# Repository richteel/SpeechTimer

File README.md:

# SpeechTimer
Clock/Timer for Speeches

# Folder Structure #

There are several folders in this project. Below is a brief description of each one.

- **CircuitPython:** An early prototype with a web interface. It works but is unstable due to memory fragmentation. It is no longer being developed. It is kept here if anyone using Python wants to use it or improve upon it.
- **Documentation:** Some documentation used during development along with user guide and other miscellaneous materials.
	- **Speech Timer - Developer Guide.docx:** Not much here at the moment. *(Just a placeholder)*
	- **Speech Timer - User Guide.docx:** Very basic user guide showing how to use the remote.
- **PCB:** Eagle project with schematic and PCB design. This is for the development version, which incorporates two Raspberry Pi Pico boards. A regular Raspberry Pi Pico as a Picoprobe and a Raspberry Pi Pico W as the micro-controller running the show.
- **SD Card:** Contents for the micro SD card.
- **SpeechTimer:** The Arduino Sketch C++ project written using the Arduino IDE. Currently everything seems to be working, but the Web Interface has not been created yet.

# Parts List #

- Raspberry Pi Pico
	- Quantity: 1
	- Note: Used as Picoprobe for programming and debugging
- Raspberry Pi Pico W
	- Quantity: 1
- 5mm Neopixels (Through hole)
	- Quantity: 58
	- Source(s): [Adafruit](https://www.adafruit.com/product/1938) / [AliExpress](https://www.aliexpress.us/item/3256804752897372.html?spm=a2g0o.order_list.order_list_main.18.3df818029J6f3W&gatewayAdapt=glo2usa)
- SD Card Breakout
	- Quantity: 1
	- Source(s): [Adafruit](https://www.adafruit.com/product/4682)
- Monochrome 0.96" 128x54 OLED Display
	- Quantity: 1
	- Source(s): [Adafruit](https://www.adafruit.com/product/326) / [Amazon](https://www.amazon.com/gp/product/B08VNRH5HR/ref=ppx_yo_dt_b_search_asin_image?ie=UTF8&th=1)
- Remote
	- Quantity: 1
	- Source(s): [Amazon](https://www.amazon.com/gp/product/B0C7BPJYH1/ref=ppx_yo_dt_b_search_asin_image?ie=UTF8&psc=1)
- 2.54mm (0.1") JST Connectors (3, 4, & 6 position)
	- Quantity: 1 each 3-position, 4-position, and 6-position
	- Source(s): [Amazon](https://www.amazon.com/gp/product/B015Y6JOUG/ref=ppx_yo_dt_b_search_asin_image?ie=UTF8&psc=1) / [AliExpress](https://www.aliexpress.us/item/2251832778234720.html?spm=a2g0o.order_detail.order_detail_item.2.2908f19cEtDDFD&gatewayAdapt=glo2usa)
- 2.54mm (0.1") Female Headers
	- Quantity: 5 (4 20-position, 1 9-position)
	- Source(s): [Adafruit](https://www.adafruit.com/product/598)
- 2.54mm (0.1") Male Headers
	- Quantity: 5 (4 20-position, 1 9-position)
	- Source(s): [Adafruit](https://www.adafruit.com/product/2671)
- Momentary Push Button Switch (N.O.) 6mm slim
	- Quantity: 2
	- Source(s): [Adafruit](https://www.adafruit.com/product/1489)
- IR Receiver TSOP38238
	- Quantity: 1
	- Source(s): [Adafruit](https://www.adafruit.com/product/157) / [AliExpress](https://www.aliexpress.us/item/2251832658861424.html?spm=a2g0o.order_list.order_list_main.12.3df818029J6f3W&gatewayAdapt=glo2usa)
- IR LED 5mm
	- Quantity: 1
	- Source(s): [Adafruit](https://www.adafruit.com/product/388)
- Red LED 3mm
	- Quantity: 1
	- Source(s): [Adafruit](https://www.adafruit.com/product/777)
- CdS Photoresistor
	- Quantity: 1
	- Source(s): [Adafruit](https://www.adafruit.com/product/161)

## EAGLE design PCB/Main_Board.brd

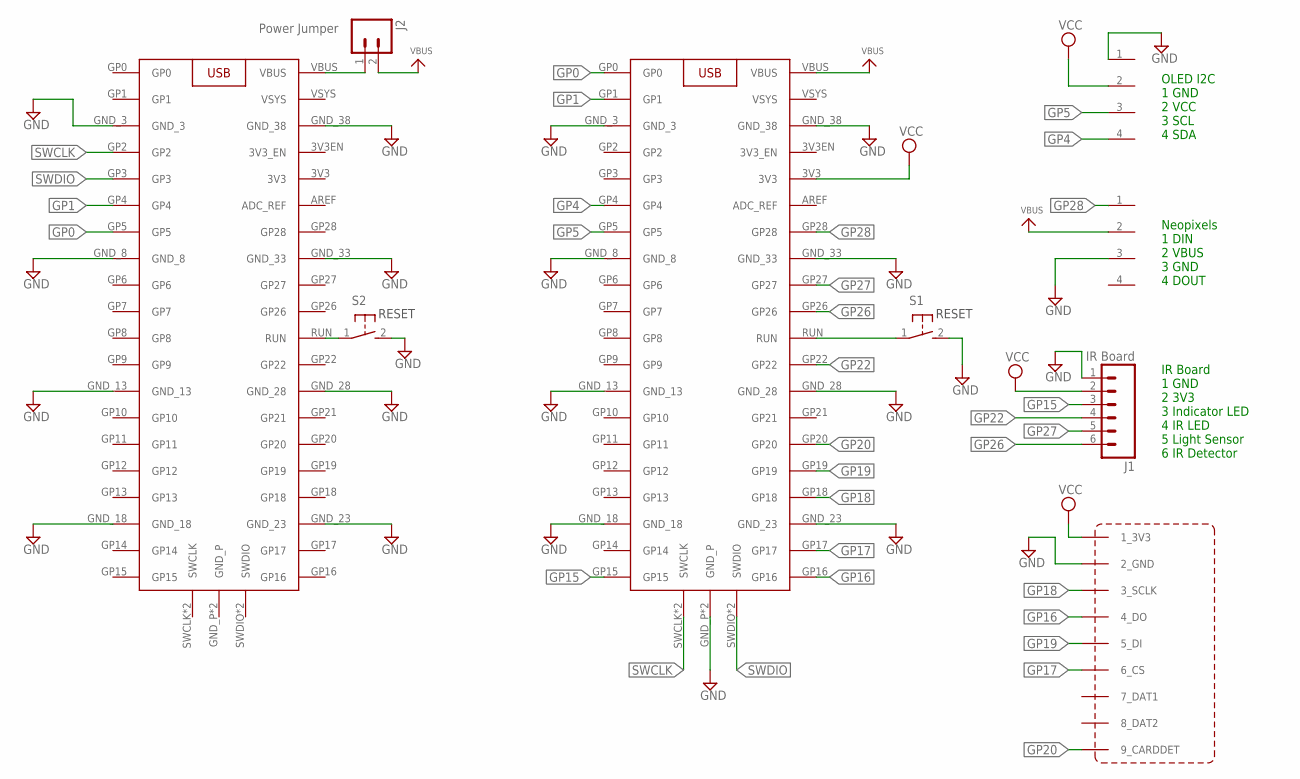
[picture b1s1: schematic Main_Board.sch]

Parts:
J1: IR Board; 1X06_LONGPADS
J2: Power Jumper; 1X02_LOCK_LONGPADS
S1, S2: RESET; ADAFRUIT_SW_1489
SDCARD2: ADAFRUIT_SDCARD3V3THROUGHHOLE; ADAFRUIT_SDCARD3V3
U$1, U$2: RASPBERRY_PI_PICORASPBERRY_PI_PICO_&_W; RASPBERRY_PI_PICO_N_W
U$3, U$4: HEADER-1X4

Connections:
GND: J1.1, S1.2 (S), S2.2 (S), SDCARD2.2_GND, U$1.GND_3, U$1.GND_8, U$1.GND_13, U$1.GND_18, U$1.GND_23, U$1.GND_28, U$1.GND_33, U$1.GND_38, U$1.GND_P, U$1.GND_P1 (GND_P), U$2.GND_3, U$2.GND_8, U$2.GND_13, U$2.GND_18, U$2.GND_23, U$2.GND_28, U$2.GND_33, U$2.GND_38, U$3.3, U$4.1
GP0: U$1.GP0, U$2.GP5
GP1: U$1.GP1, U$2.GP4
GP4: U$1.GP4, U$4.4
GP5: U$1.GP5, U$4.3
GP15: J1.3, U$1.GP15
GP16: SDCARD2.4_DO, U$1.GP16
GP17: SDCARD2.6_CS, U$1.GP17
GP18: SDCARD2.3_SCLK, U$1.GP18
GP19: SDCARD2.5_DI, U$1.GP19
GP20: SDCARD2.9_CARDDET, U$1.GP20
GP22: J1.4, U$1.GP22
GP26: J1.6, U$1.GP26
GP27: J1.5, U$1.GP27
GP28: U$1.GP28, U$3.1
unnamed: S2.1, U$2.RUN
unnamed: J2.1, U$2.VBUS
unnamed: S1.1, U$1.RUN
SWCLK: U$1.SWCLK, U$1.SWCLK1 (SWCLK), U$2.GP2
SWDIO: U$1.SWDIO, U$1.SWDIO1 (SWDIO), U$2.GP3
VBUS: J2.2, U$1.VBUS, U$3.2
VCC: J1.2, SDCARD2.1_3V3, U$1.3V3, U$4.2

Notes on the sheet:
Neopixels 1 DIN 2 VBUS 3 GND 4 DOUT
OLED I2C 1 GND 2 VCC 3 SCL 4 SDA
IR Board 1 GND 2 3V3 3 Indicator LED 4 IR LED 5 Light Sensor 6 IR Detector

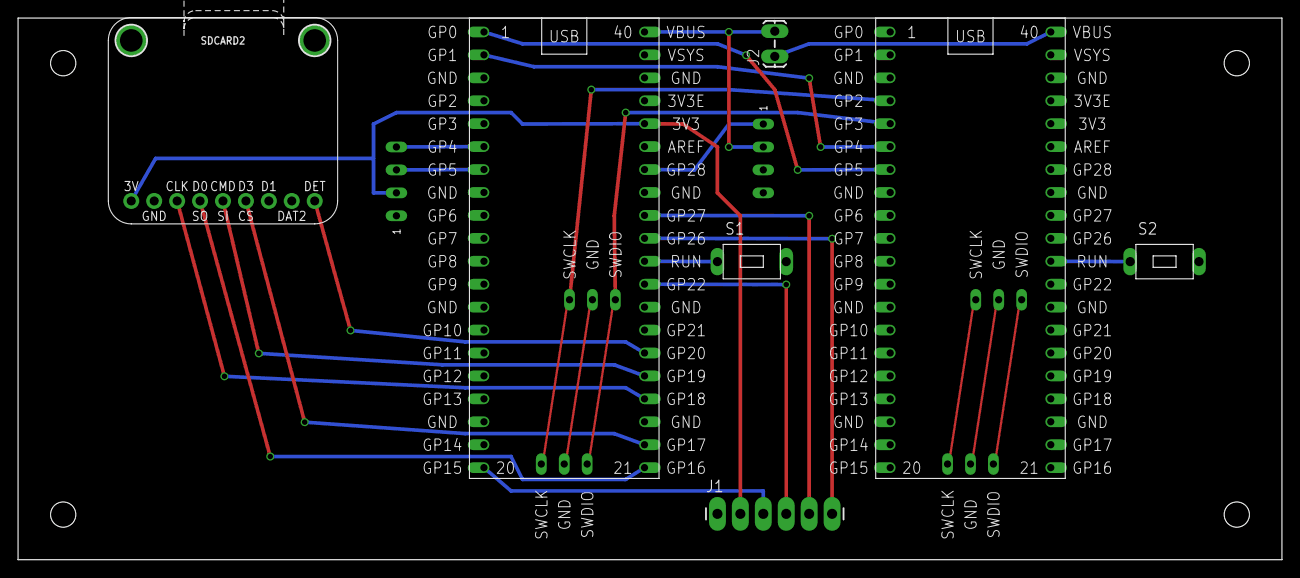
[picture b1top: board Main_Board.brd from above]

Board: 2 copper layers, 140.0 x 60.0 mm, 9 parts (0 on the bottom side), 22 nets.

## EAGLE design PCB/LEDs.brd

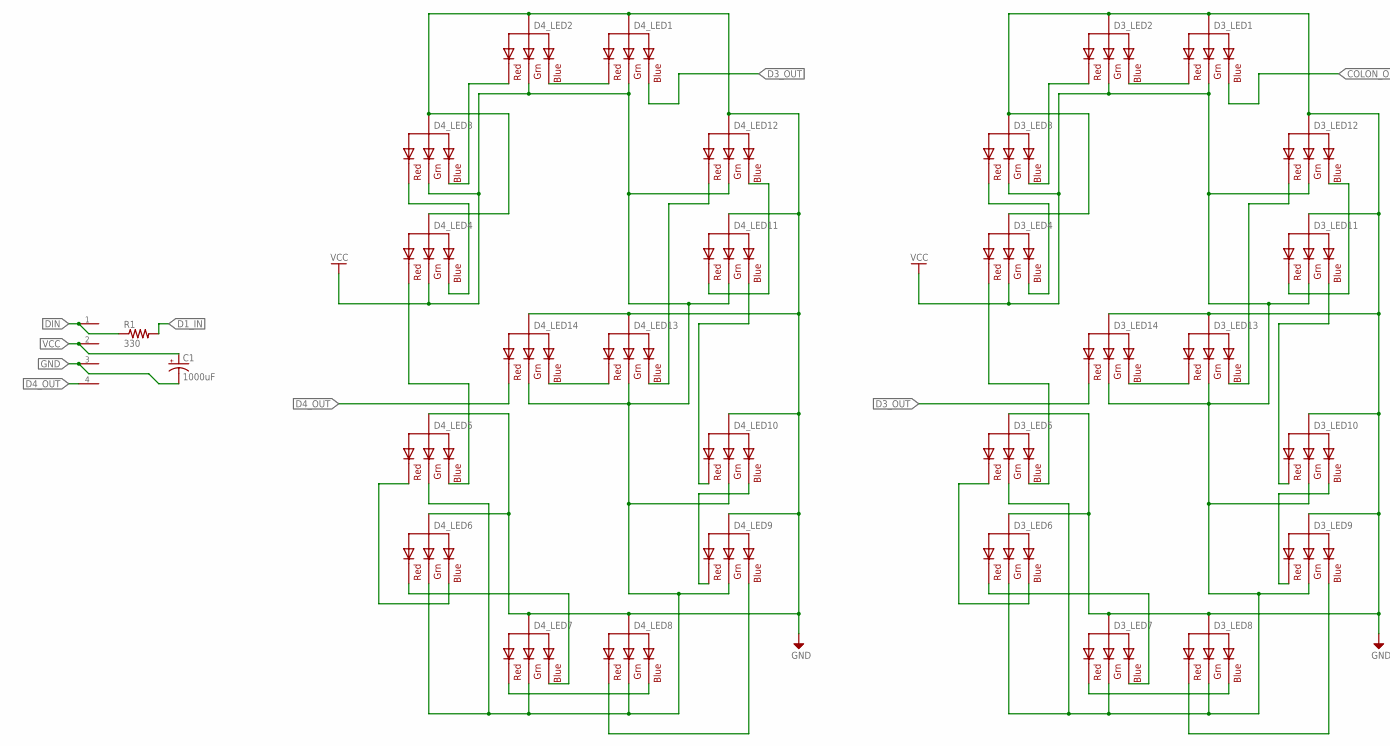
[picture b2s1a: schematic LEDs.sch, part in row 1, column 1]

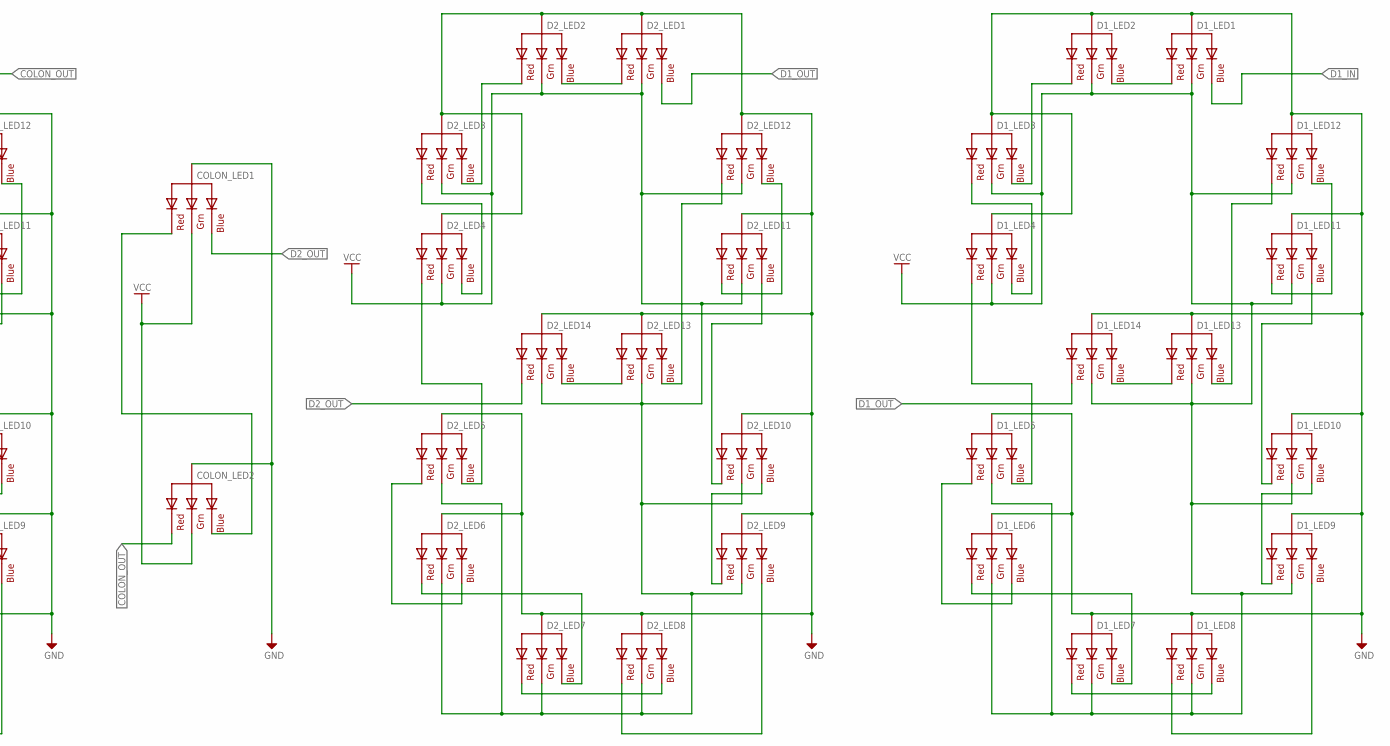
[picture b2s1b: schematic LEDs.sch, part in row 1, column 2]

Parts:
C1: 1000uF; E2,5-6
COLON_LED1, COLON_LED2: RGBLED_CA-5MM; LED5MMRGB
D1_LED1, D1_LED2, D1_LED3, D1_LED4, D1_LED5, D1_LED6, D1_LED7, D1_LED8, D1_LED9, D1_LED10, D1_LED11, D1_LED12, D1_LED13, D1_LED14, D2_LED1, D2_LED2, D2_LED3, D2_LED4, D2_LED5, D2_LED6, D2_LED7, D2_LED8, D2_LED9, D2_LED10, D2_LED11, D2_LED12, D2_LED13, D2_LED14, D3_LED1, D3_LED2, D3_LED3, D3_LED4, D3_LED5, D3_LED6, D3_LED7, D3_LED8, D3_LED9, D3_LED10, D3_LED11, D3_LED12, D3_LED13, D3_LED14, D4_LED1, D4_LED2, D4_LED3, D4_LED4, D4_LED5, D4_LED6, D4_LED7, D4_LED8, D4_LED9, D4_LED10, D4_LED11, D4_LED12, D4_LED13, D4_LED14: RGBLED_CA-5MM; LED5MMRGB
R1: 330; R0805
U$1: HEADER-1X4

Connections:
COLON_OUT: COLON_LED2.1 (RED), D3_LED1.4 (BLUE)
D1_IN: D1_LED1.4 (BLUE), R1.2
D1_OUT: D1_LED14.1 (RED), D2_LED1.4 (BLUE)
D2_OUT: COLON_LED1.4 (BLUE), D2_LED14.1 (RED)
D3_OUT: D3_LED14.1 (RED), D4_LED1.4 (BLUE)
D4_OUT: D4_LED14.1 (RED), U$1.4
DIN: R1.1, U$1.1
GND: C1.-, COLON_LED1.2 (VCC), COLON_LED2.2 (VCC), D1_LED1.2 (VCC), D1_LED2.2 (VCC), D1_LED3.2 (VCC), D1_LED4.2 (VCC), D1_LED5.2 (VCC), D1_LED6.2 (VCC), D1_LED7.2 (VCC), D1_LED8.2 (VCC), D1_LED9.2 (VCC), D1_LED10.2 (VCC), D1_LED11.2 (VCC), D1_LED12.2 (VCC), D1_LED13.2 (VCC), D1_LED14.2 (VCC), D2_LED1.2 (VCC), D2_LED2.2 (VCC), D2_LED3.2 (VCC), D2_LED4.2 (VCC), D2_LED5.2 (VCC), D2_LED6.2 (VCC), D2_LED7.2 (VCC), D2_LED8.2 (VCC), D2_LED9.2 (VCC), D2_LED10.2 (VCC), D2_LED11.2 (VCC), D2_LED12.2 (VCC), D2_LED13.2 (VCC), D2_LED14.2 (VCC), D3_LED1.2 (VCC), D3_LED2.2 (VCC), D3_LED3.2 (VCC), D3_LED4.2 (VCC), D3_LED5.2 (VCC), D3_LED6.2 (VCC), D3_LED7.2 (VCC), D3_LED8.2 (VCC), D3_LED9.2 (VCC), D3_LED10.2 (VCC), D3_LED11.2 (VCC), D3_LED12.2 (VCC), D3_LED13.2 (VCC), D3_LED14.2 (VCC), D4_LED1.2 (VCC), D4_LED2.2 (VCC), D4_LED3.2 (VCC), D4_LED4.2 (VCC), D4_LED5.2 (VCC), D4_LED6.2 (VCC), D4_LED7.2 (VCC), D4_LED8.2 (VCC), D4_LED9.2 (VCC), D4_LED10.2 (VCC), D4_LED11.2 (VCC), D4_LED12.2 (VCC), D4_LED13.2 (VCC), D4_LED14.2 (VCC), U$1.3
unnamed: D1_LED1.1 (RED), D1_LED2.4 (BLUE)
unnamed: D1_LED2.1 (RED), D1_LED3.4 (BLUE)
unnamed: D1_LED3.1 (RED), D1_LED4.4 (BLUE)
unnamed: D1_LED4.1 (RED), D1_LED5.4 (BLUE)
unnamed: D1_LED5.1 (RED), D1_LED6.4 (BLUE)
unnamed: D1_LED6.1 (RED), D1_LED7.4 (BLUE)
unnamed: D1_LED7.1 (RED), D1_LED8.4 (BLUE)
unnamed: D1_LED8.1 (RED), D1_LED9.4 (BLUE)
unnamed: D1_LED9.1 (RED), D1_LED10.4 (BLUE)
unnamed: D1_LED10.1 (RED), D1_LED11.4 (BLUE)
unnamed: D1_LED11.1 (RED), D1_LED12.4 (BLUE)
unnamed: D1_LED12.1 (RED), D1_LED13.4 (BLUE)
unnamed: D1_LED13.1 (RED), D1_LED14.4 (BLUE)
unnamed: D2_LED1.1 (RED), D2_LED2.4 (BLUE)
unnamed: D2_LED2.1 (RED), D2_LED3.4 (BLUE)
unnamed: D2_LED3.1 (RED), D2_LED4.4 (BLUE)
unnamed: D2_LED4.1 (RED), D2_LED5.4 (BLUE)
unnamed: D2_LED5.1 (RED), D2_LED6.4 (BLUE)
unnamed: D2_LED6.1 (RED), D2_LED7.4 (BLUE)
unnamed: D2_LED7.1 (RED), D2_LED8.4 (BLUE)
unnamed: D2_LED8.1 (RED), D2_LED9.4 (BLUE)
unnamed: D2_LED9.1 (RED), D2_LED10.4 (BLUE)
unnamed: D2_LED10.1 (RED), D2_LED11.4 (BLUE)
unnamed: D2_LED11.1 (RED), D2_LED12.4 (BLUE)
unnamed: D2_LED12.1 (RED), D2_LED13.4 (BLUE)
unnamed: D2_LED13.1 (RED), D2_LED14.4 (BLUE)
unnamed: D3_LED1.1 (RED), D3_LED2.4 (BLUE)
unnamed: D3_LED2.1 (RED), D3_LED3.4 (BLUE)
unnamed: D3_LED3.1 (RED), D3_LED4.4 (BLUE)
unnamed: D3_LED4.1 (RED), D3_LED5.4 (BLUE)
unnamed: D3_LED5.1 (RED), D3_LED6.4 (BLUE)
unnamed: D3_LED6.1 (RED), D3_LED7.4 (BLUE)
unnamed: D3_LED7.1 (RED), D3_LED8.4 (BLUE)
unnamed: D3_LED8.1 (RED), D3_LED9.4 (BLUE)
unnamed: D3_LED9.1 (RED), D3_LED10.4 (BLUE)
unnamed: D3_LED10.1 (RED), D3_LED11.4 (BLUE)
unnamed: D3_LED11.1 (RED), D3_LED12.4 (BLUE)
unnamed: D3_LED12.1 (RED), D3_LED13.4 (BLUE)
unnamed: D3_LED13.1 (RED), D3_LED14.4 (BLUE)
unnamed: D4_LED1.1 (RED), D4_LED2.4 (BLUE)
unnamed: D4_LED2.1 (RED), D4_LED3.4 (BLUE)
unnamed: D4_LED3.1 (RED), D4_LED4.4 (BLUE)
unnamed: D4_LED4.1 (RED), D4_LED5.4 (BLUE)
unnamed: D4_LED5.1 (RED), D4_LED6.4 (BLUE)
unnamed: D4_LED6.1 (RED), D4_LED7.4 (BLUE)
unnamed: D4_LED7.1 (RED), D4_LED8.4 (BLUE)
unnamed: D4_LED8.1 (RED), D4_LED9.4 (BLUE)
unnamed: D4_LED9.1 (RED), D4_LED10.4 (BLUE)
unnamed: D4_LED10.1 (RED), D4_LED11.4 (BLUE)
unnamed: D4_LED11.1 (RED), D4_LED12.4 (BLUE)
unnamed: D4_LED12.1 (RED), D4_LED13.4 (BLUE)
unnamed: D4_LED13.1 (RED), D4_LED14.4 (BLUE)
unnamed: COLON_LED1.1 (RED), COLON_LED2.4 (BLUE)
VCC: C1.+, COLON_LED1.3 (GREEN), COLON_LED2.3 (GREEN), D1_LED1.3 (GREEN), D1_LED2.3 (GREEN), D1_LED3.3 (GREEN), D1_LED4.3 (GREEN), D1_LED5.3 (GREEN), D1_LED6.3 (GREEN), D1_LED7.3 (GREEN), D1_LED8.3 (GREEN), D1_LED9.3 (GREEN), D1_LED10.3 (GREEN), D1_LED11.3 (GREEN), D1_LED12.3 (GREEN), D1_LED13.3 (GREEN), D1_LED14.3 (GREEN), D2_LED1.3 (GREEN), D2_LED2.3 (GREEN), D2_LED3.3 (GREEN), D2_LED4.3 (GREEN), D2_LED5.3 (GREEN), D2_LED6.3 (GREEN), D2_LED7.3 (GREEN), D2_LED8.3 (GREEN), D2_LED9.3 (GREEN), D2_LED10.3 (GREEN), D2_LED11.3 (GREEN), D2_LED12.3 (GREEN), D2_LED13.3 (GREEN), D2_LED14.3 (GREEN), D3_LED1.3 (GREEN), D3_LED2.3 (GREEN), D3_LED3.3 (GREEN), D3_LED4.3 (GREEN), D3_LED5.3 (GREEN), D3_LED6.3 (GREEN), D3_LED7.3 (GREEN), D3_LED8.3 (GREEN), D3_LED9.3 (GREEN), D3_LED10.3 (GREEN), D3_LED11.3 (GREEN), D3_LED12.3 (GREEN), D3_LED13.3 (GREEN), D3_LED14.3 (GREEN), D4_LED1.3 (GREEN), D4_LED2.3 (GREEN), D4_LED3.3 (GREEN), D4_LED4.3 (GREEN), D4_LED5.3 (GREEN), D4_LED6.3 (GREEN), D4_LED7.3 (GREEN), D4_LED8.3 (GREEN), D4_LED9.3 (GREEN), D4_LED10.3 (GREEN), D4_LED11.3 (GREEN), D4_LED12.3 (GREEN), D4_LED13.3 (GREEN), D4_LED14.3 (GREEN), U$1.2

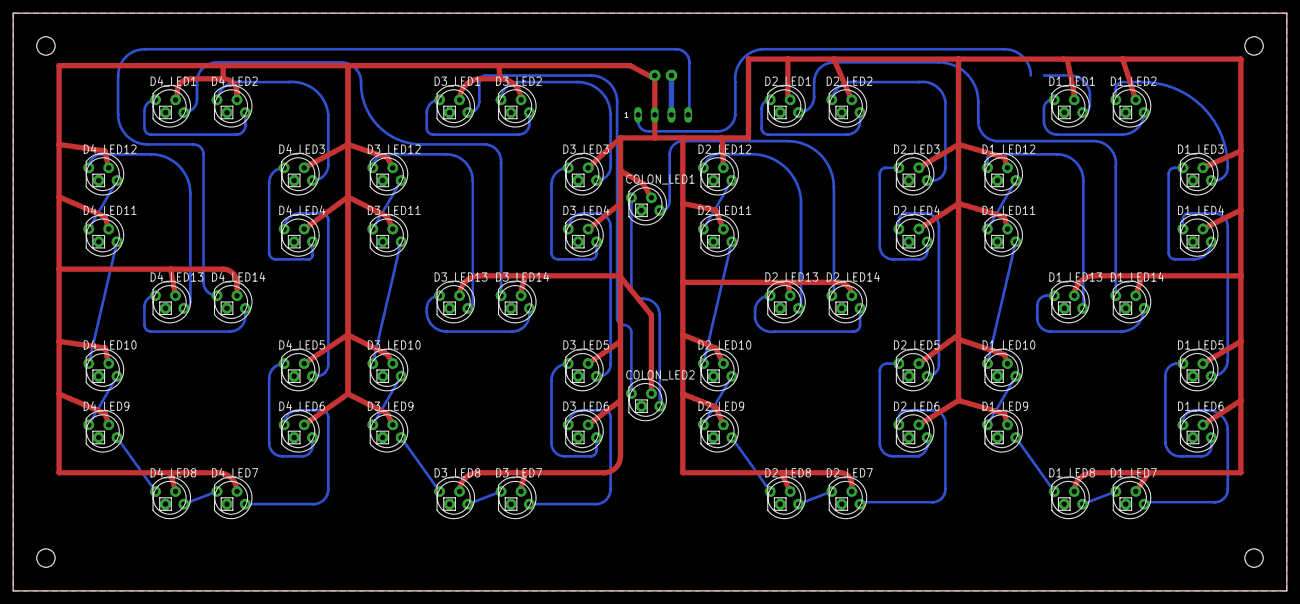
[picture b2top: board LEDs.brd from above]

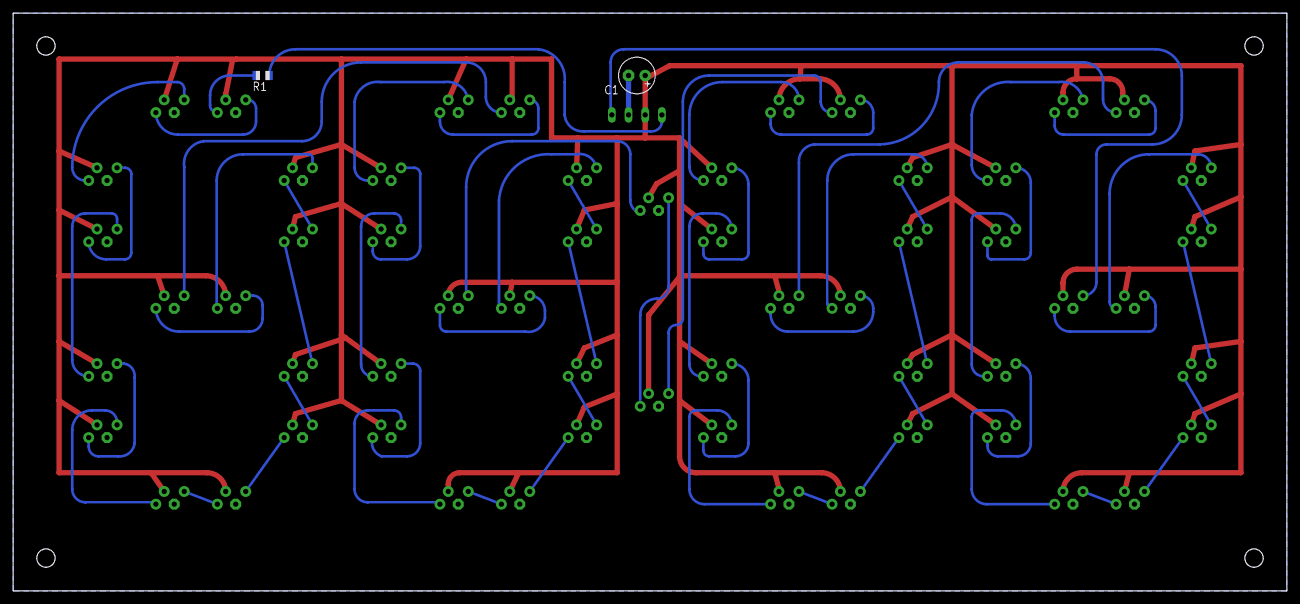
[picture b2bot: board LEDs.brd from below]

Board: 2 copper layers, 194.0 x 88.0 mm, 61 parts (2 on the bottom side), 62 nets.

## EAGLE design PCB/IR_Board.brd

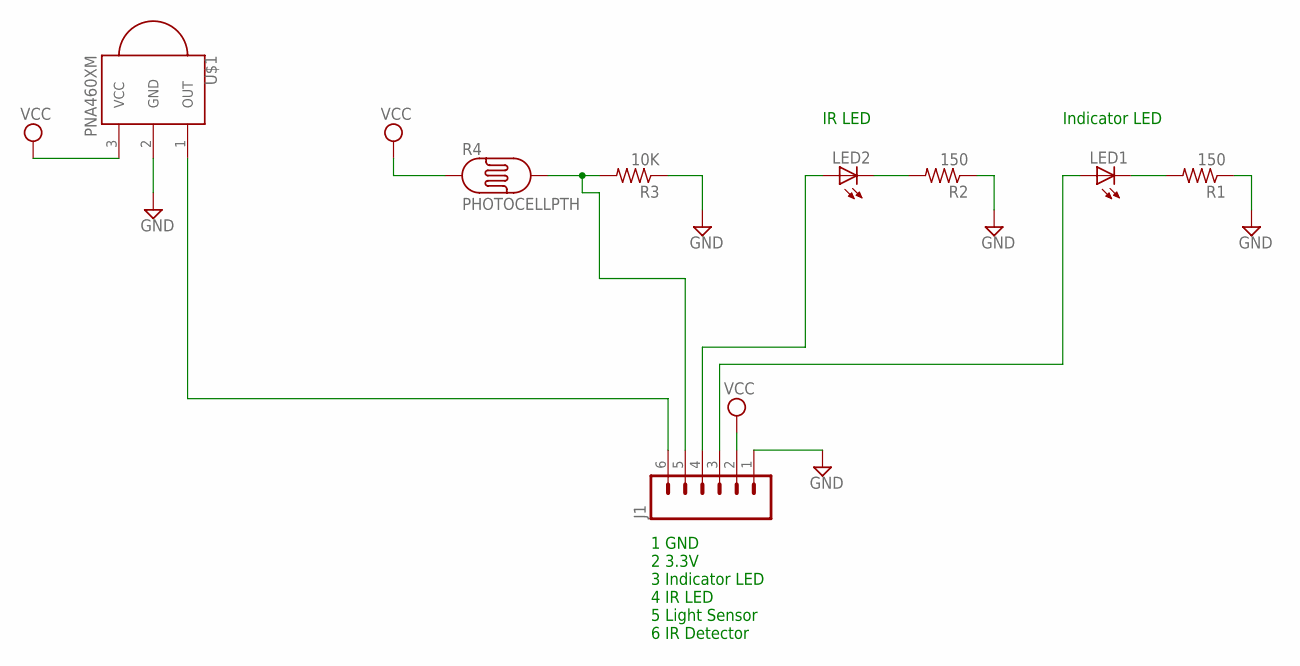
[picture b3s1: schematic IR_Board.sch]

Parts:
J1: M06LONGPADS; 1X06_LONGPADS
LED1: LED3MM
LED2: LED5MM
R1, R2: 150; M0805
R3: 10K; M0805
R4: PHOTOCELLPTH; PHOTOCELL
U$1: PNA460XM

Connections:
GND: J1.1, R1.1, R2.1, R3.1, U$1.2 (GND)
unnamed: J1.5, R3.2, R4.2
unnamed: LED2.K (C), R2.2
unnamed: LED1.K (C), R1.2
unnamed: J1.3, LED1.A
unnamed: J1.4, LED2.A
unnamed: J1.6, U$1.1 (OUT)
VCC: J1.2, R4.1, U$1.3 (VCC)

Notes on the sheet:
IR LED
Indicator LED
1 GND 2 3.3V 3 Indicator LED 4 IR LED 5 Light Sensor 6 IR Detector

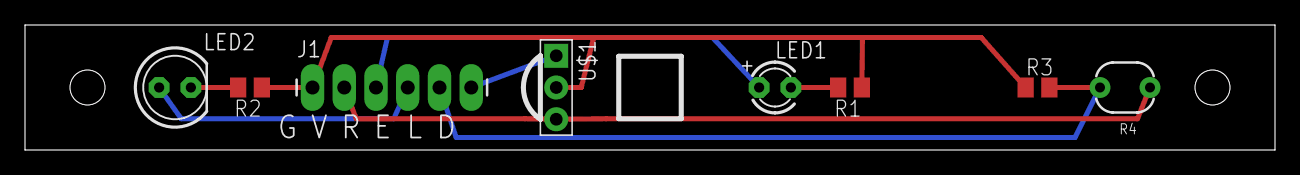
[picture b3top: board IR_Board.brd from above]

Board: 2 copper layers, 100.0 x 10.0 mm, 8 parts (0 on the bottom side), 8 nets.

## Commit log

2023-09-16 Initial code with CircuitPython project
2023-09-17 - Load and Save Configuration - Run Tests on SD card
2023-09-23 Completed SDD Card, WiFi (Connect & Client only), and RTC Tests have been added for each item
2023-09-23 Adding sample test output
2023-09-25 Clock now functioning. Still a lot of work to do but getting closer.
2023-09-26 Started incorporating the OLED Display
2023-09-27 OLED Display now showing IP Address and time with seconds
2023-09-28 - Turned off Test and Debug - Replaced Serial.print statements with debug D_print statements - Found an error with the WiFi library, which requires that Serial.begin is called. Edited code to call Se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
2023-09-30 Fixed a problem with disabling the use of Serial.print, which caused WiFi connection code to be skipped. It appears that milllis() may reset to zero only when Serial.begin() is called. If it is not c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
2023-10-09 Added remote
2023-10-14 - Adding PCB and Schematic - Adding latest software changes
2023-10-25 Adding FreeRTOS version. Expect to move forward with FreeRTOS.
2023-12-11 Arduino C++ version working, but without web client
2026-02-13 Updates based on AI Code Review
2026-02-14 Working code with updates. The display now turn green when connected to WiFi before getting the latest time from http://worldtimeapi.org/.
2026-02-14 Removed CircuitPython version as it will no longer be supported. Added web-server to control the clock from a web page.
2026-02-14 Ignore private files
2026-02-17 Updates for stability and bug fixes.
2026-02-18 Made a few more improvements to stability
2026-02-19 Additional stability edits for the WebServer

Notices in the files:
parts and their libraries:
SparkFun-Connectors: Licensing: Creative Commons ShareAlike 4.0 International - https://creativecommons.org/licenses/by-sa/4.0
m-pad-2.1: License : GNU General Public License version 2 (see bottom)
